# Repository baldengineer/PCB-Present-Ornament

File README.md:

## KiCad Present / Ornament
KiCad stuff.

## Warning: JST is not compatible with Adafruit batteries. + and - are reversed :(

* LED Matrix
* ATmega8 (328) based
* Powered by LiPo
* Programmed with ISP Header
* hand it with a string around the ribbon loops

## Bald Engineer Live Stream
Watch the stream and help out in chat here:
https://twitch.tv/baldengineer

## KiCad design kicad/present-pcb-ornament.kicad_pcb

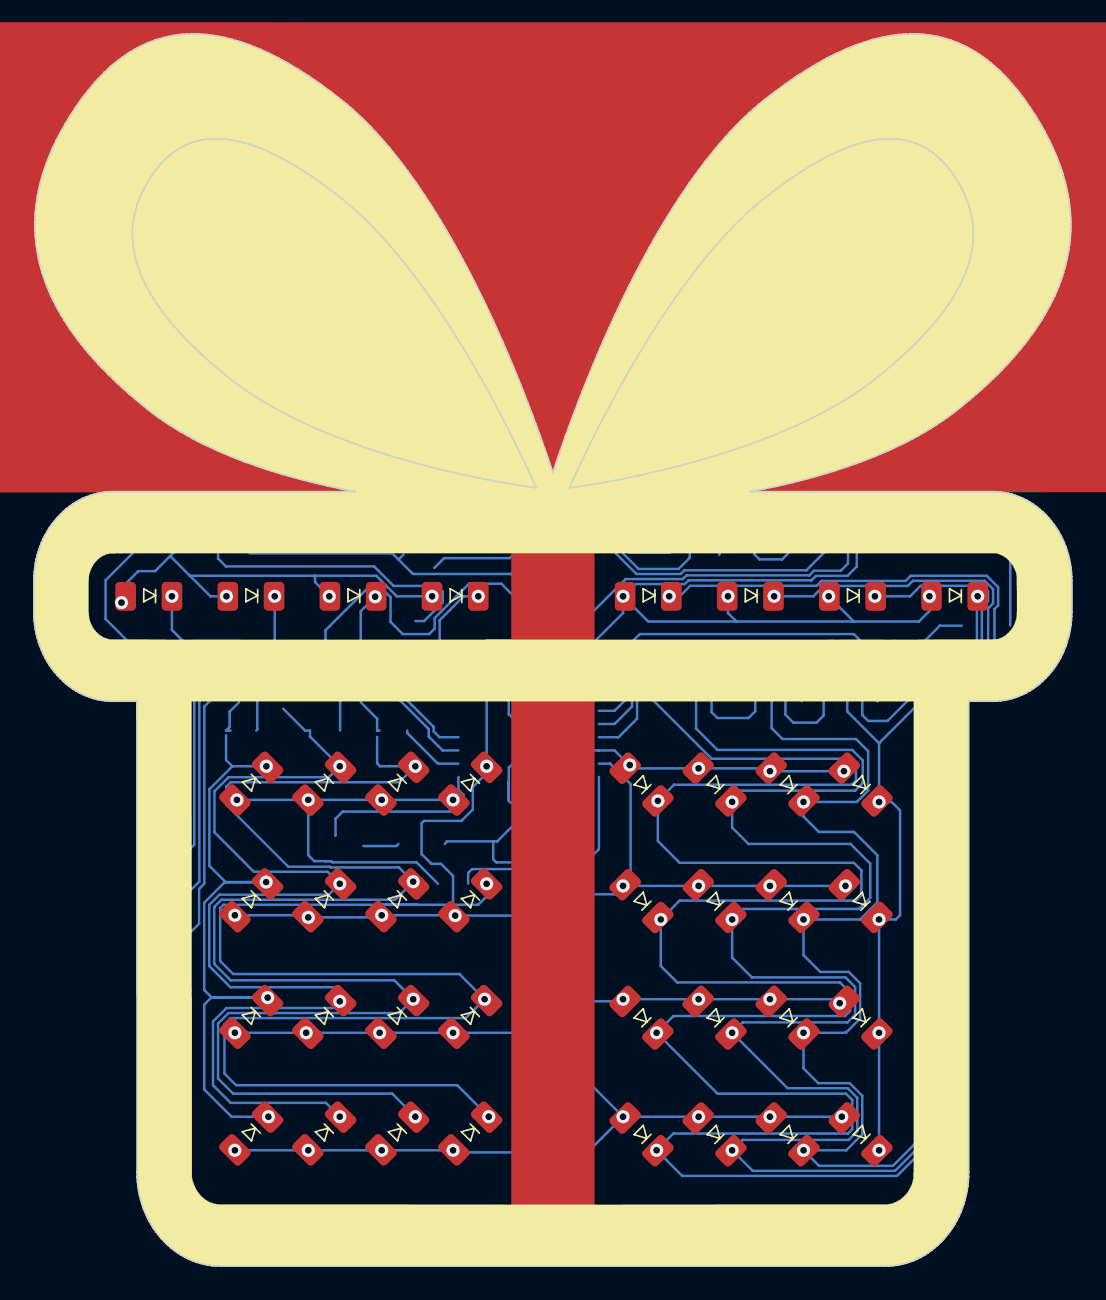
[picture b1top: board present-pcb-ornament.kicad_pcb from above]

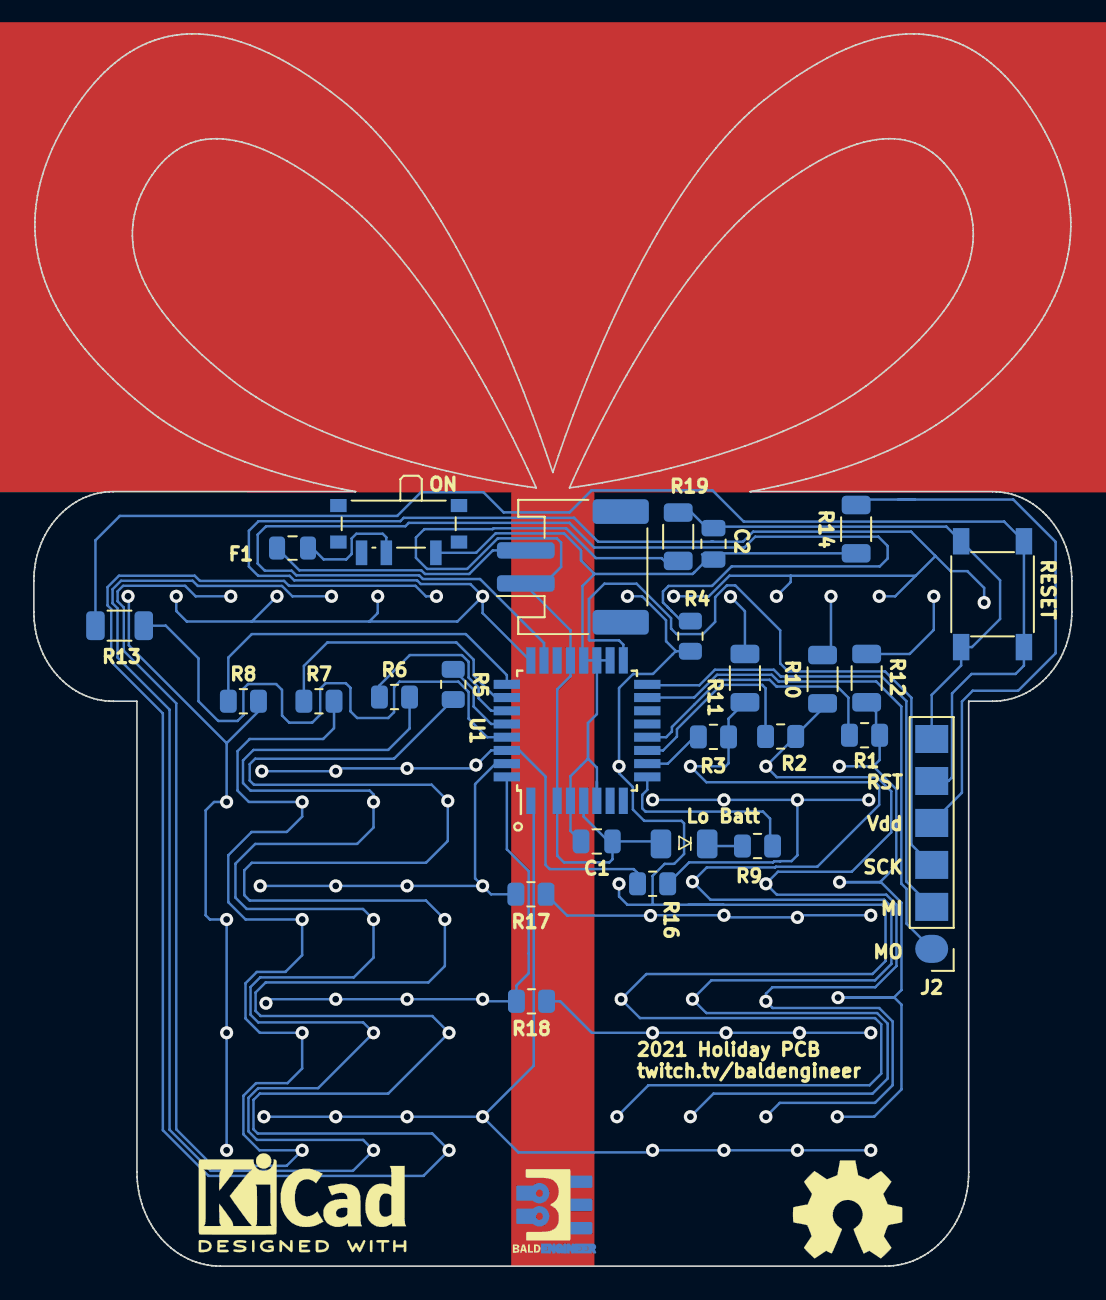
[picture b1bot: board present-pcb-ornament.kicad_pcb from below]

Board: 2 copper layers, 62.8 x 74.6 mm, 69 parts (28 on the bottom side), 31 nets.

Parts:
C1, C2: 10u; C_0805_2012Metric
D1, D34, D35, D36, D37, D38, D39, D40, D41: RED; LED_1206_3216Metric-NoSilk
D2, D3, D4, D5, D6, D7, D8, D9, D10, D11, D12, D13, D14, D15, D16, D17, D18, D19, D20, D21, D22, D23, D24, D25, D26, D27, D28, D29, D30, D31, D32: GRN; LED_1206_3216Metric-NoSilk
D33: Batt; LED_1206_3216Metric-NoSilk
F1: 200mA; Fuse_0805_2012Metric
H1: PCB; inky escaped
J1: Batt; JST_PH_S2B-PH-SM4-TB_1x02-1MP_P2.00mm_Horizontal
J2: ISP; PinHeader_1x06_P2.54mm_SMD_Field
R1, R2, R3, R4, R5, R6, R7, R8: R_0805; R_0805_2012Metric
R9: 1K; R_0805_2012Metric
R10, R11, R12, R13, R14, R19: 0; R_1206_3216Metric
R16, R17, R18: 0; R_0805_2012Metric
SW1: PWR; SW_SPDT_PCM12-no-mounts
SW2: RESET; SW_Push_CK_PTS525_SM15
U1: ATmega8A-AU; TQFP-32_7x7mm_P0.8mm
svg2mod: G***; BE5v2

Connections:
/Fused: F1.2, SW1.2
/MISO: J2.2, U1.16
/MOSI: J2.1, U1.15
/Pin1: R1.1, U1.12
/Pin2: R2.1, U1.11
/Pin3: R3.1, U1.10
/Pin4: R4.1, U1.23
/Pin5: R5.1, U1.28
/Pin6: R6.1, U1.27
/Pin7: R7.1, U1.26
/Pin8: R8.1, U1.25
/Pin9: D34.1, D35.1, D36.1, D37.1, D38.1, D39.1, D40.1, D41.1, U1.24
/Pin10: D1.1, D5.1, D9.1, D13.1, D17.1, D21.1, D25.1, D29.1, R16.1, R16.2, U1.30
/Pin11: D2.1, D6.1, D10.1, D14.1, D18.1, D22.1, D26.1, D30.1, R17.1, R17.2, U1.31
/Pin12: D3.1, D7.1, D11.1, D15.1, D19.1, D23.1, D27.1, D31.1, R18.1, R18.2, U1.32
/Pin13: D4.1, D8.1, D12.1, D16.1, D20.1, D24.1, D28.1, D32.1, U1.1
/Pin17: R9.2, U1.9
/RESET: J2.5, R13.1, R13.2, SW2.2, U1.29
/SCK: J2.3, U1.17
/Vin: F1.1, J1.2
/nR1: D1.2, D2.2, D3.2, D4.2, D34.2, R1.2, R12.1, R12.2
/nR2: D5.2, D6.2, D7.2, D8.2, D35.2, R2.2, R10.1, R10.2
/nR3: D9.2, D10.2, D11.2, D12.2, D36.2, R3.2, R11.1, R11.2
/nR4: D13.2, D14.2, D15.2, D16.2, D37.2, R4.2
/nR5: D17.2, D18.2, D19.2, D20.2, D38.2, R5.2
/nR6: D21.2, D22.2, D23.2, D24.2, D39.2, R6.2
/nR7: D25.2, D26.2, D27.2, D28.2, D40.2, R7.2
/nR8: D29.2, D30.2, D31.2, D32.2, D41.2, R8.2
GND: C1.2, C2.2, D33.1, J1.1, J2.6, R19.1, R19.2, SW2.1, U1.3, U1.5, U1.21
unnamed: D33.2, R9.1
VDD: C1.1, C2.1, J2.4, R14.1, R14.2, SW1.1, U1.4, U1.6, U1.18, U1.19, U1.20

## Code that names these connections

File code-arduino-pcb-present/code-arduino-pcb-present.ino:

// Bald Engineer's Live PCB Present Ornament
// James Lewis (C) 2021
// MIT License

// Get the MiniCore Board Definitions! 
// Boards have a 168P or 328PB 3v3 @ 8 MHz
// We're going to run with internal RC oscillator
//
// The PCBs have 40 LEDs configured as a matrix with 
// 8 columns and 5 rows. Code below turns on two LEDs
// at a time. Direct port manipulation limits the flicker.

// #include<EEPROM.h>

// Define the pinouts
// Rows
// PCB: Pin9, Pin10, Pin11, Pin12, Pin13
// AVR: PC1,  PD0,   PD1,   PD2,   PD3
// Uno: A1,    0,     1,     2,     3
const byte row_count = 5;
const byte rows[row_count] = {A1,0,1,2,3};

// Cols
// PCB: Pin1, Pin2, Pin3, Pin4, Pin5, Pin6, Pin7, Pin8
// AVR: PB0,  PD7,  PD6,  PC0,  PC5,  PC4,  PC3,  PC2
// Uno:   8,    7,    6,    A0,  A5,   A4,   A3,   A2
const byte col_count = 8;
const byte cols[8] = {8,7,6,A0,A5,A4,A3,A2};

// Pointless Battery Stuff
// Just realized, I tied AREF to ADC6
// batt_pointless has a LED, so it can be used for debug
const byte batt_facepalm = A6; // ADC
const byte batt_pointless = 5; // PD5

uint8_t mode = 0; // was going to cycle patterns on boot

// Cols    0     1     2     3     4    5      6     7
// PCB: Pin1, Pin2, Pin3, Pin4, Pin5, Pin6, Pin7, Pin8
// AVR: PB0,  PD7,  PD6,  PC0,  PC5,  PC4,  PC3,  PC2
// Uno:   8,    7,    6,    A0,  A5,   A4,   A3,   A2
void drive_col(int row, unsigned long led_wait_time) {
  pinMode(row, OUTPUT);
  digitalWrite(row, LOW);

  // we have plenty of flash memory available

  // DDR = 1 is out, 0 is in  
  // col Pin1 PB0
  DDRB = DDRB | 0x01; // col is out
  PORTB = PORTB | 0x01; // turn it on
  delayMicroseconds(led_wait_time);
  DDRB = DDRB & 0xFE; // col is in

  // col Pin2 PD7
  DDRD = DDRD | 0x80; // col is out
  PORTD = PORTD | 0x80; // turn it on
  delayMicroseconds(led_wait_time);
  DDRD = DDRD & 0x7F; // col is in 

  // col Pin3 PD6
  DDRD = DDRD | 0x40; // col is out
  PORTD = PORTD | 0x40; // turn it on
  delayMicroseconds(led_wait_time);
  DDRD = DDRD & 0xBF; // col is in 

  // col Pin4 PC0
  DDRC = DDRC | 0x01; // col is out
  PORTC = PORTC | 0x01; // turn it on
  delayMicroseconds(led_wait_time);
  DDRC = DDRC & 0xFE; // col is in 

  // col Pin5 PC5
  DDRC = DDRC | 0x20; // col is out
  PORTC = PORTC | 0x20; // turn it on
  delayMicroseconds(led_wait_time);
  DDRC = DDRC & 0xDF; // col is in 

  // col Pin6 PC4
  DDRC = DDRC | 0x10; // col is out
  PORTC = PORTC | 0x10; // turn it on
  delayMicroseconds(led_wait_time);
  DDRC = DDRC & 0xEF; // col is in 

  // col Pin7 PC3
  DDRC = DDRC | 0x08; // col is out
  PORTC = PORTC | 0x08; // turn it on
  delayMicroseconds(led_wait_time);
  DDRC = DDRC & 0xF7; // col is in 
  
  // col Pin8 PC2
  DDRC = DDRC | 0x04; // col is out
  PORTC = PORTC | 0x04; // turn it on
  delayMicroseconds(led_wait_time);
  DDRC = DDRC & 0xFB; // col is in 

  pinMode(row, INPUT);
}

void setup() {
  mode = -1; // eventually replace with EEPROM code
}

void loop() {
 for (int row=0; row < row_count; row++) {
    drive_col(rows[row], 250);
  }
}

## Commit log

2021-12-16 initial commit (project already fabbed)
2021-12-20 Some initial Arduino code, totally untested.
2021-12-20 iBOM for Bald Pick and Place, follow along!
2021-12-20 they all turn on... yay!
2021-12-20 removing commented out BHAGs
2021-12-20 simplified basic code
2021-12-20 new header image
2022-01-03 Added image to document where to connect power.
